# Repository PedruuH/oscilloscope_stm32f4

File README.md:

# Oscilloscope with STM32F411

### Introdução

Projeto de hardware criado para cumprimento curricular da materia de [Sistemas Embarcados](https://www.sei.ufu.br/sei/modulos/pesquisa/md_pesq_documento_consulta_externa.php?9LibXMqGnN7gSpLFOOgUQFziRouBJ5VnVL5b7-UrE5TaLVb9Ob-k1xeZzwpJhfKB5Qjsj8a9MYiml2zMNhVGjwljS_oCJB1WK3ClZbhIeKMX95mtj1gVD4zkyVOHL9-R). Neste repositório possui a cocepção de três possiveis roteamentos de trilhas em PCB, sendo o [segundo](https://github.com/PedruuH/oscilloscope_stm32f4/blob/main/oscilloscope_stm32F4%20-%202.kicad_pcb) o adotado como final.

### Imagens da PCB

Parte superior:

Parte inferior:

### Fabricação

Foram gerados os Gerbers de fabricação e se encontram na pasta [Fabricação](https://github.com/PedruuH/oscilloscope_stm32f4/tree/main/Fabrica%C3%A7%C3%A3o), contudo, é fortemente recomendado abrir o projeto e adaptar o PCB de acordo com a empresa de fabricação de sua escolha.

### Software usado

Utilizado a ferramenta open source de design de eletronicos [KiCad 5.1.10](https://www.kicad.org/).

# Licensing

Copyright 2020 Pedro Henrique R M Santos.

Licensed under the Apache License, Version 2.0 (the "License");

you may not use this file except in compliance with the License.

You may obtain a copy of the License at [http://www.apache.org/licenses/LICENSE-2.0](http://www.apache.org/licenses/LICENSE-2.0)

Unless required by applicable law or agreed to in writing, software

distributed under the License is distributed on an "AS IS" BASIS,

WITHOUT WARRANTIES OR CONDITIONS OF ANY KIND, either express or implied.

See the License for the specific language governing permissions and

limitations under the License.

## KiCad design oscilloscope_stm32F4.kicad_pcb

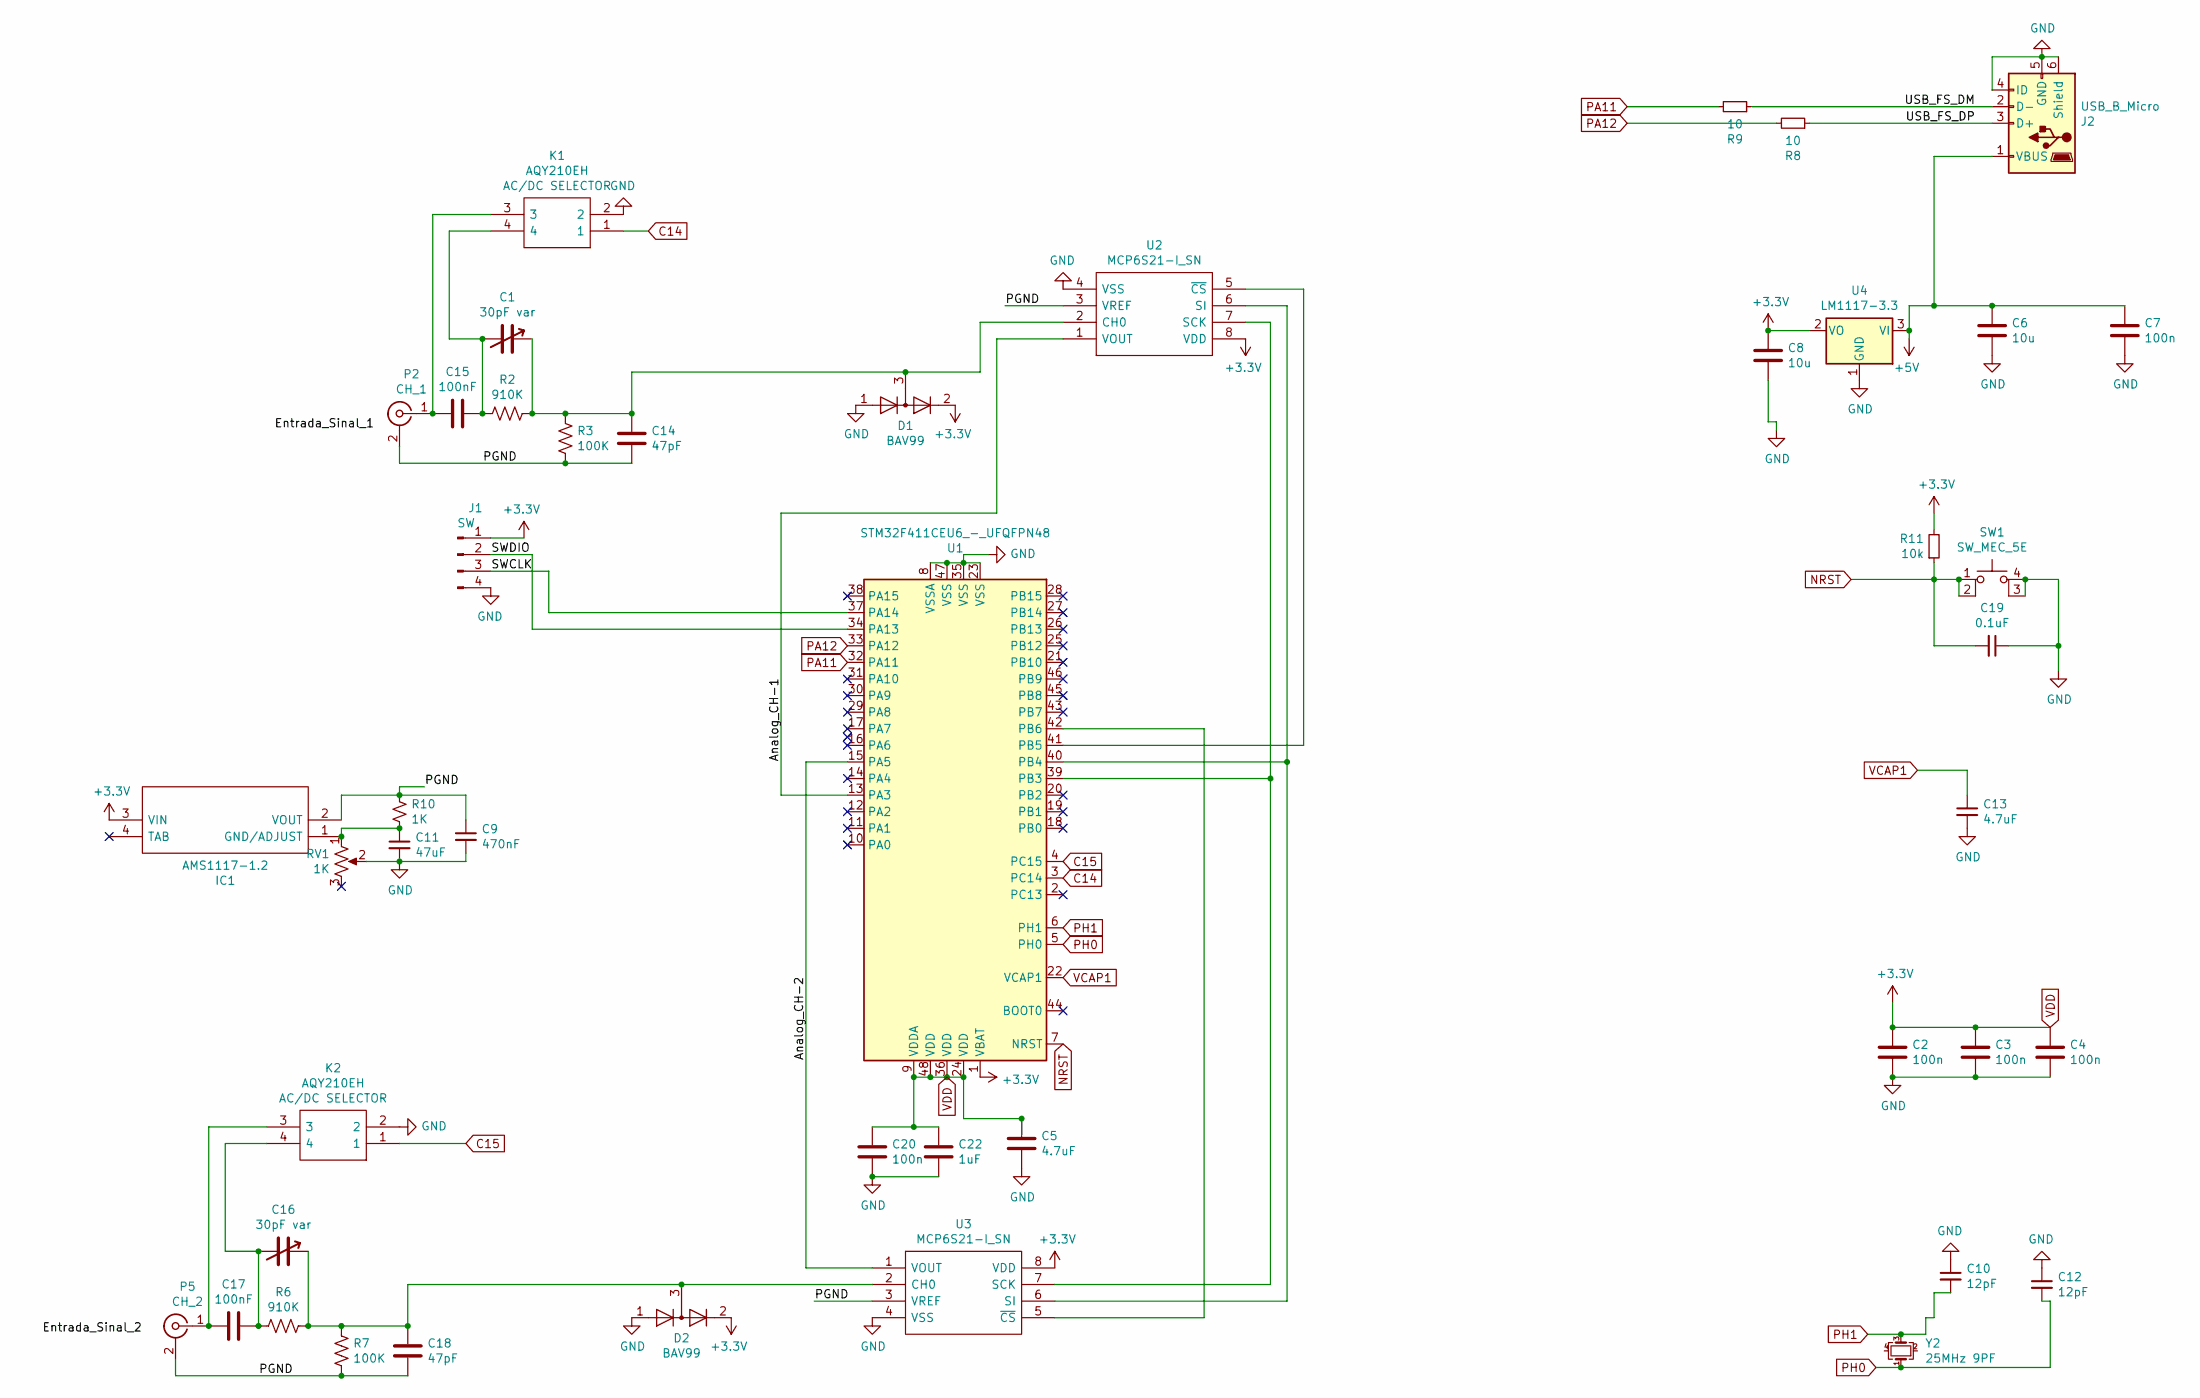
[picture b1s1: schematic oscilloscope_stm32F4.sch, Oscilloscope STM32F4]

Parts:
C1, C16: 30pF var; JZ300
C2, C3, C4, C7, C20: 100n; C_0805_2012Metric_Pad1.18x1.45mm_HandSolder
C5, C13: 4.7uF; C_0805_2012Metric_Pad1.18x1.45mm_HandSolder
C6, C8: 10u; C_1210_3225Metric_Pad1.33x2.70mm_HandSolder
C9: 470nF; CAPC1005X55N
C10, C12: 12pF; C_0603_1608Metric_Pad1.08x0.95mm_HandSolder
C11: 47uF; CP_EIA-7132-20_AVX-U
C14, C18: 47pF; C_0603_1608Metric_Pad1.08x0.95mm_HandSolder
C15, C17: 100nF; C_0805_2012Metric_Pad1.18x1.45mm_HandSolder
C19: 0.1uF; C_0805_2012Metric_Pad1.18x1.45mm_HandSolder
C22: 1uF; C_0805_2012Metric_Pad1.18x1.45mm_HandSolder
D1, D2: BAV99; SOT-23
IC1: AMS1117-1.2; SOT229P700X180-4N; Manufacturer_Part_Number AMS1117-1.2
J1: SW; PinSocket_1x04_P2.54mm_Vertical
J2: USB_B_Micro; USB_Micro-B_Amphenol_10103594-0001LF_Horizontal
K1, K2: AQY210EH; DIP762W47P254L478H340Q4N; Mouser Part Number 769-AQY210EH
P2: CH_1; BNC_Amphenol_B6252HB-NPP3G-50_Horizontal
P5: CH_2; BNC_Amphenol_B6252HB-NPP3G-50_Horizontal
R2, R6: 910K; R_1210_3225Metric_Pad1.30x2.65mm_HandSolder
R3, R7: 100K; R_2512_6332Metric_Pad1.40x3.35mm_HandSolder
R8, R9: 10; R_Axial_DIN0204_L3.6mm_D1.6mm_P5.08mm_Horizontal
R10: 1K; R_Axial_DIN0204_L3.6mm_D1.6mm_P5.08mm_Horizontal
R11: 10k; R_Axial_DIN0204_L3.6mm_D1.6mm_P5.08mm_Horizontal
RV1: 1K; Potentiometer_Bourns_3266Y_Vertical
SW1: SW_MEC_5E; SW_SPST_Omron_B3FS-100xP
U1: STM32F411CEU6_-_UFQFPN48; QFN-48-1EP_7x7mm_P0.5mm_EP5.6x5.6mm
U2, U3: MCP6S21-I_SN; SOIC127P600X175-8N; Manufacturer_Part_Number MCP6S21-I/SN; Mouser Part Number 579-MCP6S21-I/SN
U4: LM1117-3.3; SOT-223-3_TabPin2
Y2: 25MHz 9PF; CrystalSMD

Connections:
+5V: C6.1, C7.1, J2.1 (VBUS), U4.3 (VI)
/Analog_CH-1: U1.13 (PA3), U2.1 (VOUT)
/Analog_CH-2: U1.15 (PA5), U3.1 (VOUT)
/PGND: C9.1, C14.2, C18.2, IC1.2 (VOUT), P2.2 (Ext), P5.2 (Ext), R3.2, R7.2, R10.1, U2.3 (VREF), U3.3 (VREF)
/SWCLK: J1.3, U1.37 (PA14)
/SWDIO: J1.2, U1.34 (PA13)
/USB_FS_DM: J2.2 (D-), R9.1
/USB_FS_DP: J2.3 (D+), R8.1
C14: K1.1, U1.3 (PC14)
C15: K2.1, U1.4 (PC15)
GND: C2.2, C3.2, C4.2, C5.2, C6.2, C7.2, C8.2, C9.2, C10.1, C11.2, C12.1, C13.2, C19.1, C20.2, C22.2, D1.1 (K), D2.1 (K), J1.4, J2.4 (ID), J2.5 (GND), J2.6 (Shield), K1.2, K2.2, RV1.2, SW1.3 (K), SW1.4 (A), U1.8 (VSSA), U1.23 (VSS), U1.35 (VSS), U1.47 (VSS), U2.4 (VSS), U3.4 (VSS), U4.1 (GND)
NRST: C19.2, R11.1, SW1.1, SW1.2, U1.7 (NRST)
unnamed: C1.1, C14.1, D1.3 (K), R2.1, R3.1, U2.2 (CH0)
unnamed: C1.2, C15.1, K1.4, R2.2
unnamed: C11.1, IC1.1 (GND/ADJUST), R10.2, RV1.1
unnamed: C15.2, K1.3, P2.1 (In)
unnamed: C16.1, C18.1, D2.3 (K), R6.1, R7.1, U3.2 (CH0)
unnamed: C16.2, C17.1, K2.4, R6.2
unnamed: C17.2, K2.3, P5.1 (In)
unnamed: U1.39 (PB3), U2.7 (SCK), U3.7 (SCK)
unnamed: U1.40 (PB4), U2.6 (SI), U3.6 (SI)
unnamed: U1.41 (PB5), U2.5 (~CS)
unnamed: U1.42 (PB6), U3.5 (~CS)
PA11: R9.2, U1.32 (PA11)
PA12: R8.2, U1.33 (PA12)
PH0: C12.2, U1.5 (PH0), Y2.1
PH1: C10.2, U1.6 (PH1), Y2.3
VCAP1: C13.1, U1.22 (VCAP1)
VDD: C2.1, C3.1, C4.1, C5.1, C8.1, C20.1, C22.1, D1.2 (A), D2.2 (A), IC1.3 (VIN), J1.1, R11.2, U1.1 (VBAT), U1.9 (VDDA), U1.24 (VDD), U1.36 (VDD), U1.48 (VDD), U2.8 (VDD), U3.8 (VDD), U4.2 (VO)

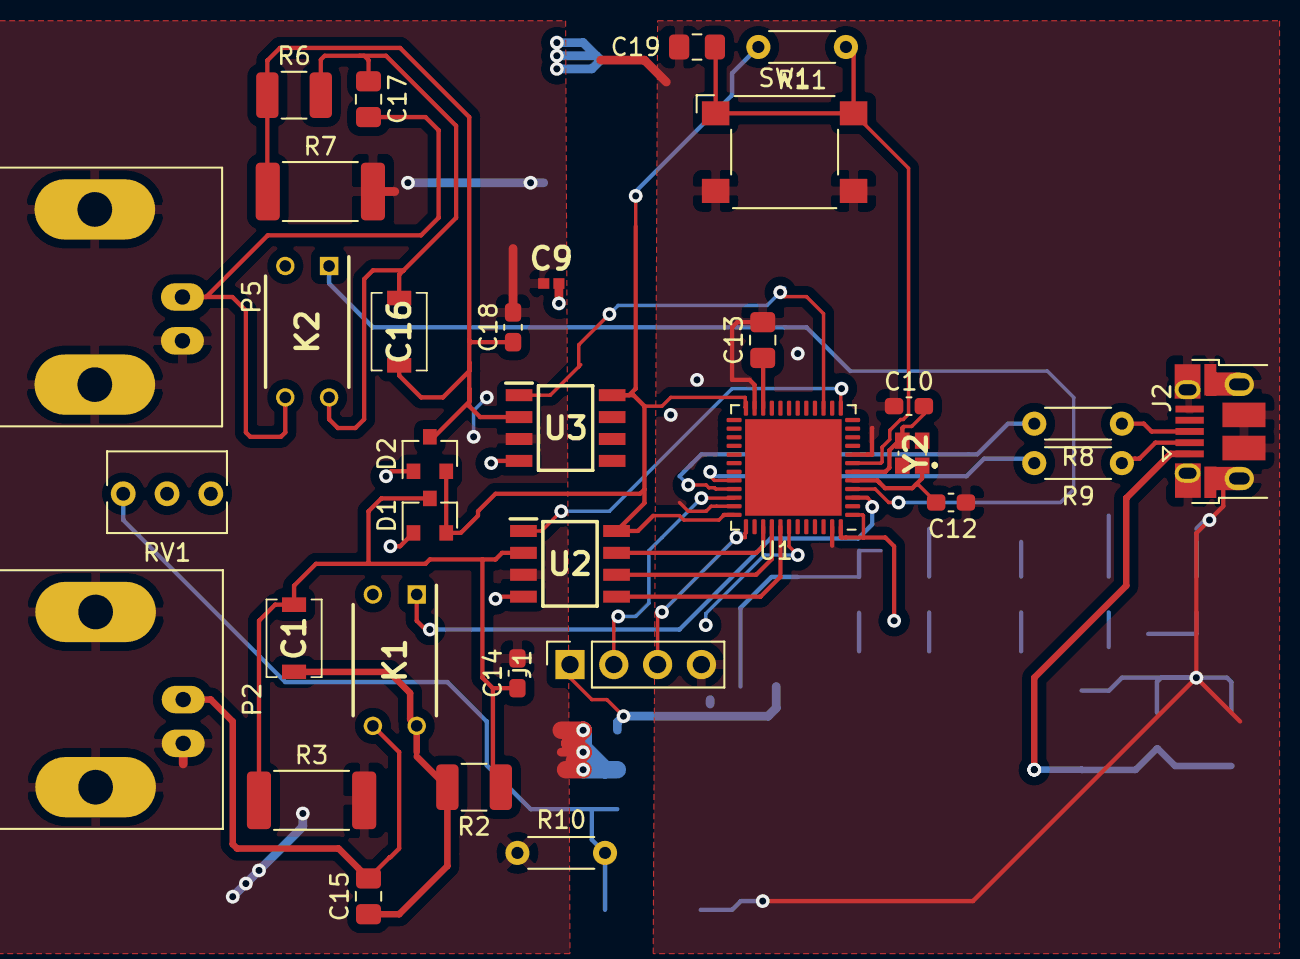
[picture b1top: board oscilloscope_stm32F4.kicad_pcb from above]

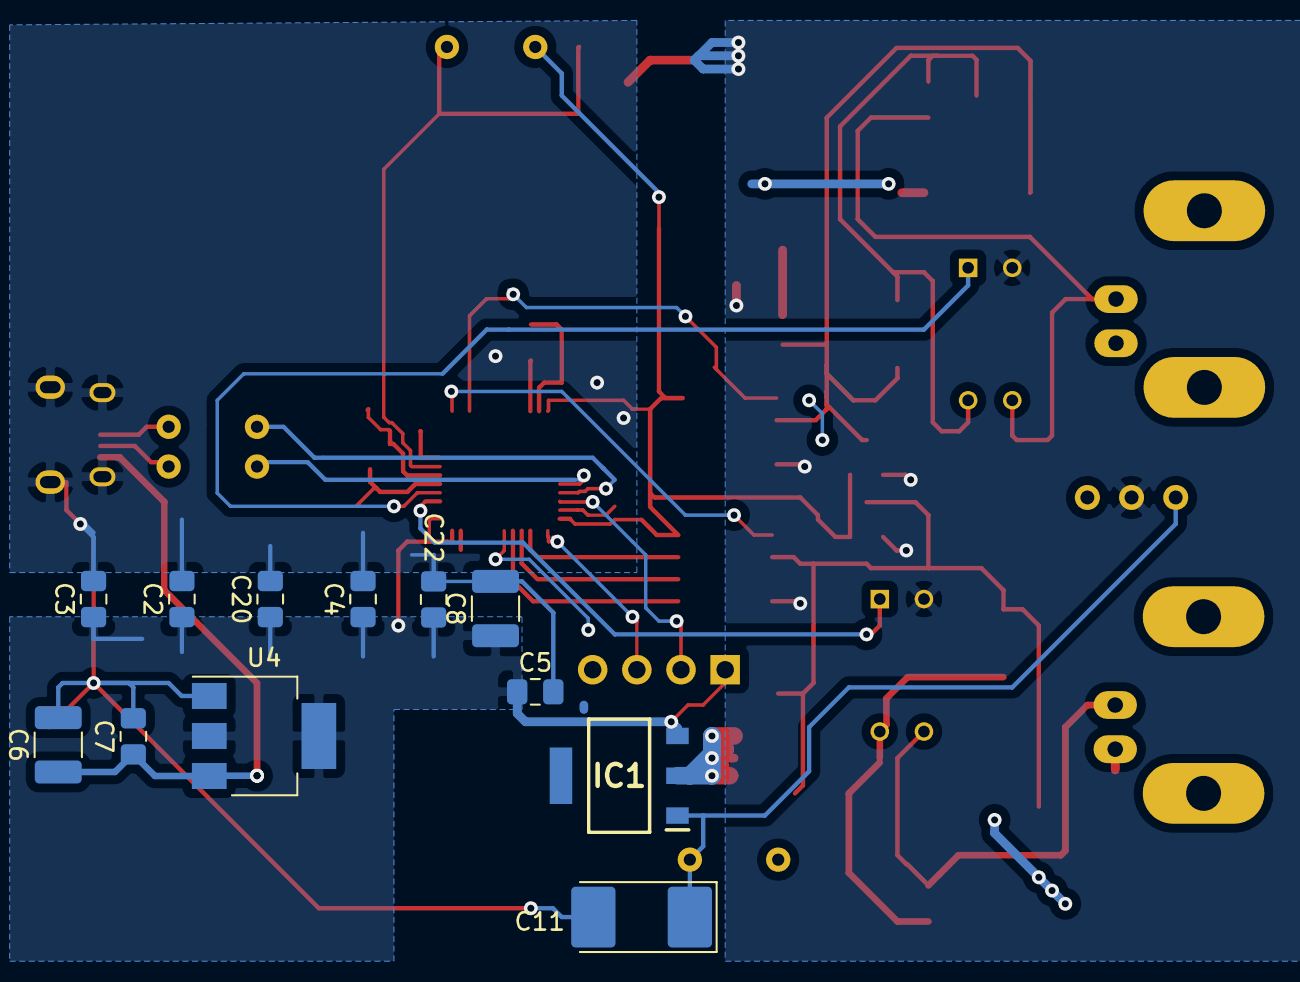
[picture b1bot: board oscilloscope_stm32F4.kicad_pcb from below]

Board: 2 copper layers, 45 parts (12 on the bottom side), 29 nets.

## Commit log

2021-05-07 Inicio Projeto
2021-05-08 atualização
2021-05-11 Atualizando...
2021-07-04 final
2021-10-24 exclude paste oscilloscope_stm32f4
2021-10-24 new images and drl
2021-10-24 update image
2021-10-24 update image top
